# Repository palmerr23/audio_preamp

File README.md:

# audio_preamp
pro grade dual mic-instrument preamp runs off 5V

Designed to complement the audio ADC boards such as the Teensy Audio Board, this pro-grade dual mic/instrument preamp features:
- Single 5v supply operation
- Output aligned to common microcontroller ADC levels (1v RMS, drive loads > 2000 ohms)
- Combo TRS/XLR input jack to save panel space with automatic mic/inst switching 
- 0-20dB gain on instrument channel (1M ohm input impedance)
- Independent +48V phantom power for each mic channel
- THAT1512 mic preamp for optimum performance
- 20 & 40dB switched gain mic channel + 0-20dB gain control (overall gain 20-60dB)

Attached board files are in Eagle 9.0 format

Two 'off the shelf' switching regulator modules power the preamp:
- a +/-15V (often marked DD1718) and a +35 boost regulator based on the XL6007/9 chips. Image files are included, above.

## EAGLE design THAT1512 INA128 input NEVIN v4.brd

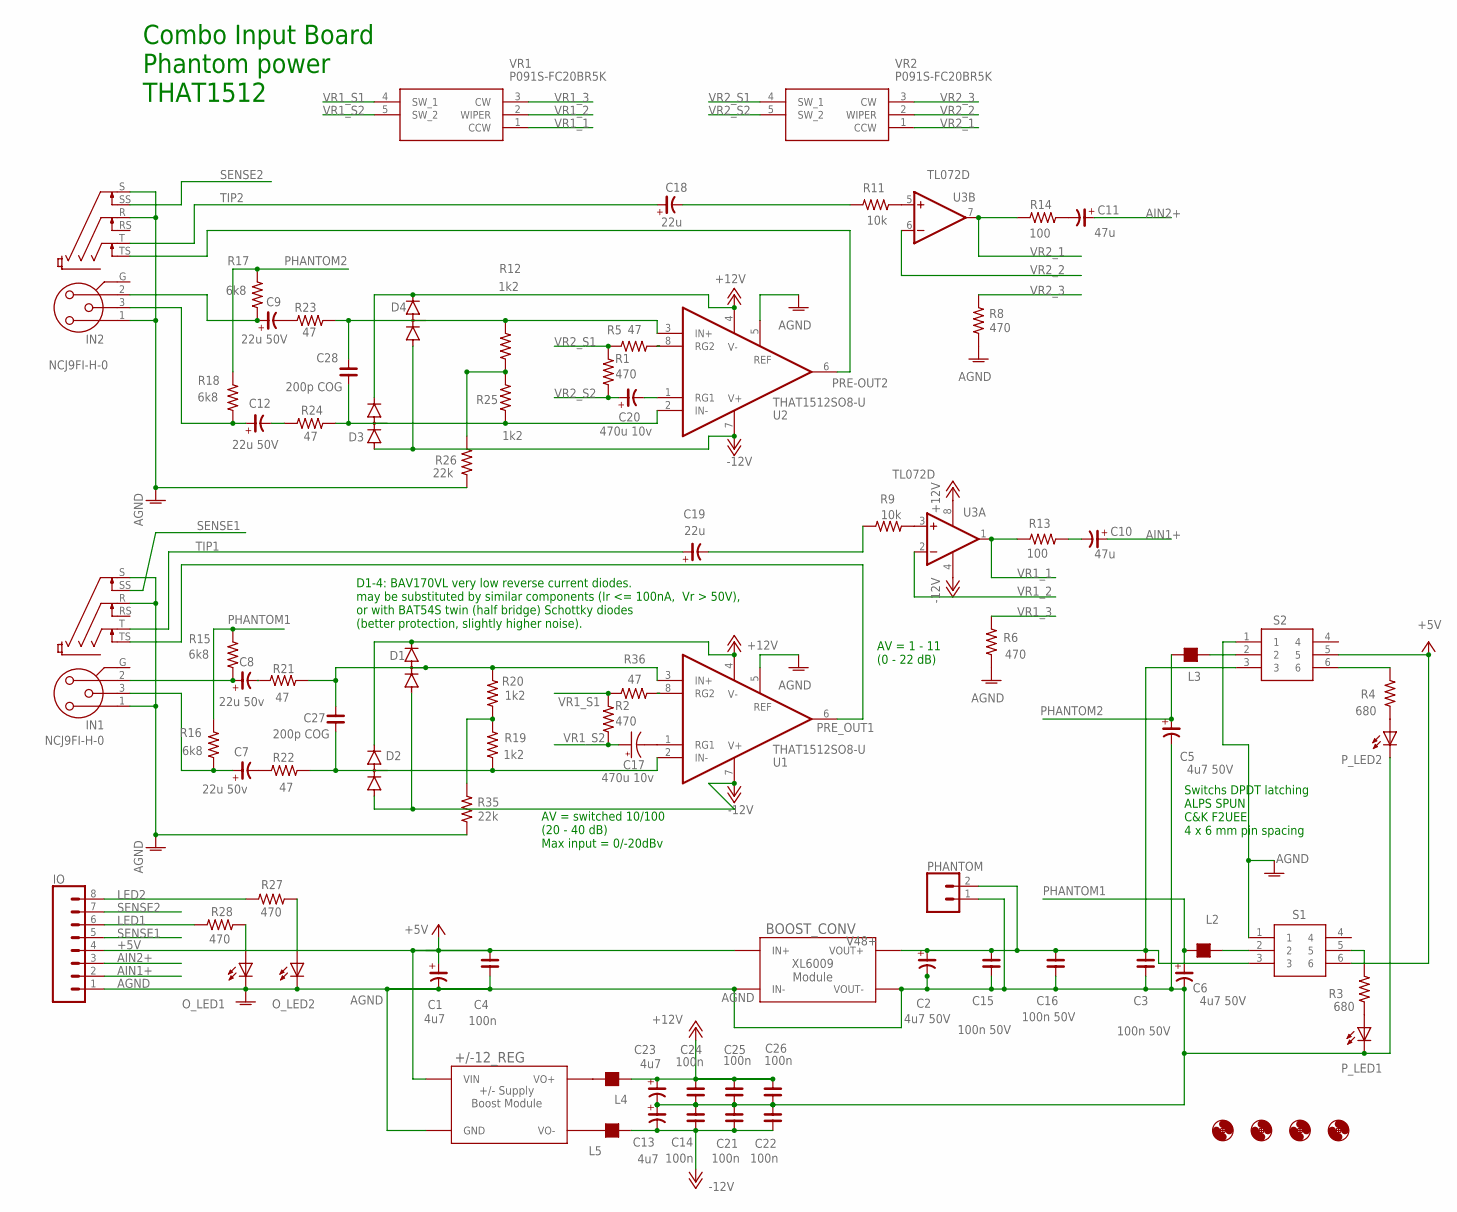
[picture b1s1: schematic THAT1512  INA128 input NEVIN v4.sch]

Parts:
+/-12_REG: POS_NEG_SUP_MODULE; POS_NEG_SUP_MODULE_F
BOOST_CONV: XL6009_MODULE; XL6009_MODULE_F
C1, C13, C23: 4u7; C3216/T
C2, C5, C6: 4u7 50V; C3216/T
C3, C15, C16: 100n 50V; C0805
C4, C14, C21, C22, C24, C25, C26: 100n; C0805
C7, C8: 22u 50v; CSV-C
C9, C12: 22u 50V; CSV-C
C10, C11: 47u; CSV-B
C17: 470u 10v; 153CLV-0605
C18, C19: 22u; CSV-B
C20: 470u 10v; CSV-C
C27, C28: 200p COG; C0805
D1, D2, D3, D4: HSMS-285C; SOT323
H1, H2, H3, H4: MOUNT-HOLE3.6; 3,6
IN1, IN2: NCJ9FI-H-0; NCJ9FI-H
IO: CONN_08"; 1X08
L2, L3, L4, L5: 150; L0805
O_LED1, O_LED2: LED3MM
PHANTOM: CONN_02; 1X02
P_LED1, P_LED2: LED3MM
R1, R2, R6, R8, R27, R28: 470; R0805
R3, R4: 680; R0805
R5, R21, R22, R23, R24, R36: 47; R0805
R9, R11: 10k; R0805
R12, R19, R20, R25: 1k2; R0805
R13, R14: 100; R0805
R15, R16, R17, R18: 6k8; R0805
R26, R35: 22k; R0805
S1, S2: SPUN191600; SPUN191000
U1, U2: THAT1512SO8-U; SO08
U3: TL072D; SO08
VR1, VR2: P091S-FC20BR5K; P091SFC20BR5K

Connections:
+5V: +/-12_REG.IN+ (VIN), BOOST_CONV.IN+, C1.+, C4.2, IO.4, S1.6, S2.5
+12V: C23.+, C24.2, C25.2, C26.2, D1.2 (C), D2.2 (C), D3.2 (C), D4.2 (C), L4.1, U1.4 (V-), U2.4 (V-), U3.8 (V+)
-12V: C13.-, C14.1, C21.1, C22.1, D1.1 (A), D2.1 (A), D3.1 (A), D4.1 (A), L5.1, U1.7 (V+), U2.7 (V+), U3.4 (V-)
AGND: +/-12_REG.GND, +/-12_REG.GND@1 (GND), BOOST_CONV.IN-, BOOST_CONV.VOUT-, C1.-, C2.-, C3.1, C4.1, C5.-, C6.-, C13.+, C14.2, C15.1, C16.1, C21.2, C22.2, C23.-, C24.1, C25.1, C26.1, IN1.1, IN1.R, IN1.S, IN2.1, IN2.R, IN2.S, IO.1, O_LED1.K (C), O_LED2.K (C), PHANTOM.1, P_LED1.K (C), P_LED2.K (C), R6.2, R8.2, R26.2, R35.2, S1.1, S2.1, U1.5 (REF), U2.5 (REF)
AIN1+: C10.+, IO.2
AIN2+: C11.+, IO.3
LED1: IO.6, R28.2
LED2: IO.8, R27.2
unnamed: C27.2, D1.3 (AC), R20.1, R21.1, U1.3 (IN+)
unnamed: C27.1, D2.3 (AC), R19.2, R22.1, U1.2 (IN-)
unnamed: C28.2, D4.3 (AC), R12.1, R23.1, U2.3 (IN+)
unnamed: R36.2, U1.8 (RG2)
unnamed: L2.1, S1.2
unnamed: P_LED1.A, R3.1
unnamed: L3.1, S2.2
unnamed: R9.1, U3.3 (+IN)
unnamed: P_LED2.A, R4.1
unnamed: R11.1, U3.5 (+IN)
unnamed: R5.2, U2.8 (RG2)
unnamed: R3.2, S1.5
unnamed: R4.2, S2.6
unnamed: C18.-, R11.2
unnamed: +/-12_REG.VO-, L5.2
unnamed: C7.-, R22.2
unnamed: +/-12_REG.VO+, L4.2
unnamed: C11.-, R14.1
unnamed: C10.-, R13.1
unnamed: C7.+, IN1.3, R16.1
unnamed: C8.-, R21.2
unnamed: C8.+, IN1.2, R15.1
unnamed: C9.-, R23.2
unnamed: C12.-, R24.2
unnamed: C9.+, IN2.2, R17.1
unnamed: C12.+, IN2.3, R18.1
unnamed: C28.1, D3.3 (AC), R24.1, R25.2, U2.2 (IN-)
unnamed: C19.-, R9.2
unnamed: O_LED1.A, R28.1
unnamed: O_LED2.A, R27.1
unnamed: R19.1, R20.2, R35.1
unnamed: C17.-, U1.1 (RG1)
unnamed: C20.-, U2.1 (RG1)
unnamed: R12.2, R25.1, R26.1
PHANTOM1: C6.+, L2.2, R15.2, R16.2
PHANTOM2: C5.+, L3.2, R17.2, R18.2
PRE-OUT2: IN2.TS, U2.6 (OUT)
PRE_OUT1: IN1.TS, U1.6 (OUT)
SENSE1: IN1.SS, IO.5
SENSE2: IN2.SS, IO.7
TIP1: C19.+, IN1.T
TIP2: C18.+, IN2.T
V48+: BOOST_CONV.VOUT+, C2.+, C3.2, C15.2, C16.2, PHANTOM.2, S1.3, S2.3
VR1_1: R13.2, U3.1 (OUT), VR1.1 (CCW)
VR1_2: U3.2 (-IN), VR1.2 (WIPER)
VR1_3: R6.1, VR1.3 (CW)
VR1_S1: R2.1, R36.1, VR1.4 (SW_1)
VR1_S2: C17.+, R2.2, VR1.5 (SW_2)
VR2_1: R14.2, U3.7 (OUT), VR2.1 (CCW)
VR2_2: U3.6 (-IN), VR2.2 (WIPER)
VR2_3: R8.1, VR2.3 (CW)
VR2_S1: R1.1, R5.1, VR2.4 (SW_1)
VR2_S2: C20.+, R1.2, VR2.5 (SW_2)

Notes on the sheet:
Combo Input Board Phantom power THAT1512
AV = switched 10/100 (20 - 40 dB) Max input = 0/-20dBv
Switchs DPDT latching ALPS SPUN C&K F2UEE 4 x 6 mm pin spacing
AV = 1 - 11 (0 - 22 dB)
D1-4: BAV170VL very low reverse current diodes. may be substituted by similar components (Ir <= 100nA, Vr > 50V), or with BAT54S twin (half bridge) Schottky diodes (better protection, slightly higher noise).

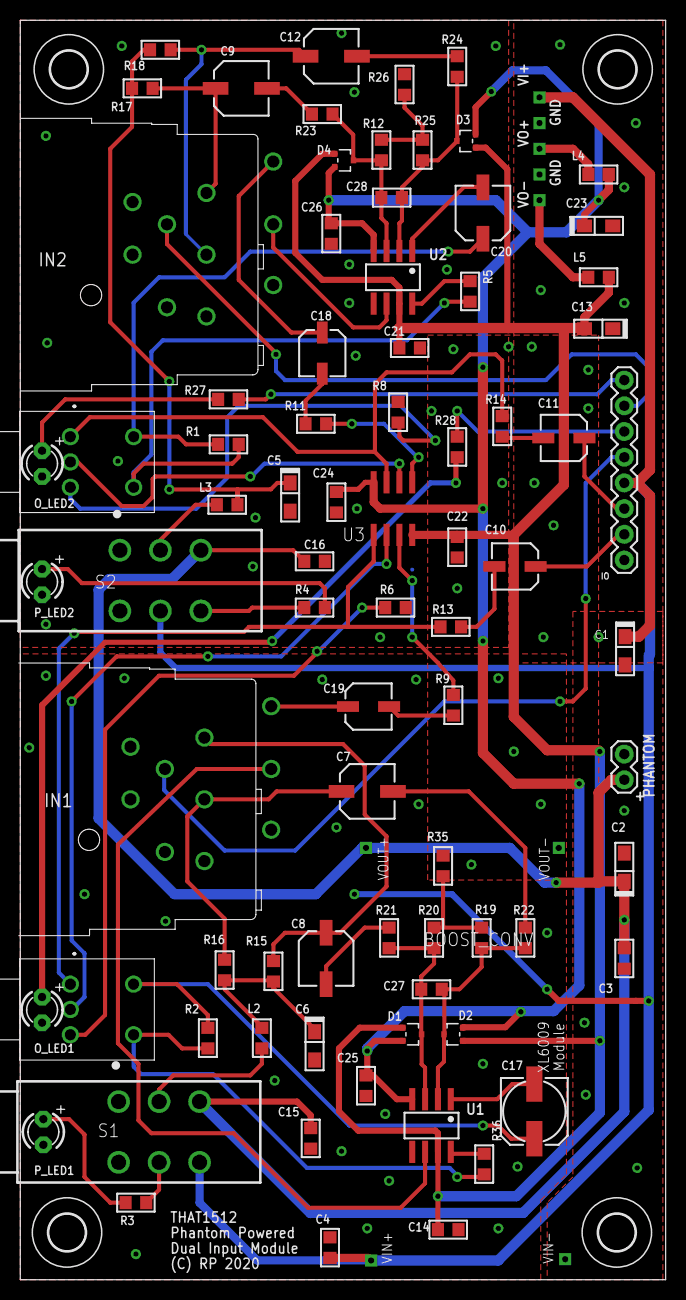
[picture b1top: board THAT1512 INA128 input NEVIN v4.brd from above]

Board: 2 copper layers, 63.8 x 124.5 mm, 85 parts (1 on the bottom side), 61 nets.

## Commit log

2020-05-16 Fixed routing
2020-05-16 improved component placement and labeling
2020-05-16 Improved notes
2020-05-16 visualisation added
2020-05-17 power supply images

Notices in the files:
parts and their libraries:
SparkFun-Connectors: Licensing: Creative Commons ShareAlike 4.0 International - https://creativecommons.org/licenses/by-sa/4.0
rc-master-smd: Copyright (C) 2007, Bob Starr
that-corp: Copyright (C) 2008-2010, Bob Starr
